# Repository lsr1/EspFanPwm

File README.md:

# EspFanPwm

control speed of one to three fans via PWM (9BMB12P2K01) and get the tacho signal, using a D1 mini with [ESPHome](https://esphome.io/) via [Home Assistant](https://www.home-assistant.io/). 

## Executive Summary
* This project offers a solution for providing the same speed signal to up to three fans (9BMB12P2K01) with Home Assistant (via ESPHome), utilizing a D1 mini board.
* This project consists of a KiCad project that gives you the [Gerber files](gerber/gerber.zip) to order a PCB (e.g. at [JLCPCB](https://cart.jlcpcb.com)) onto which (mostly) passive components (pinheaders/sockets) are soldered. Then you plug on some standard modules you can get from [AliExpress](https://www.aliexpress.com), create a device in Home Assistant and are pretty much done.
* For the impatient: Go to [Installation](#Installation).

## Picture

## Sidenotes
This is my third "public GitHub" project. Yeah, I copy/paste a lot of these READMEs... I made something (crude) that I nevertheless think might be useful for somebody else - this time, I think the audience is rather small, but I am publishing it regardless :-). As usual, this readme will be rather long - I want to document the story behind it for my records.</br>
Despite the verbosity of the README, it assumes that you know how to solder, how to work with a multimeter and your way around Home Assistant and ESPHome. Some things here are weirdly specific, while some are infuriatingly generic (assuming a lot of knowhow).

## Preamble (Why)
I did this because a crate of 9BMB12P2K01 fans fell from a truck and into my lap. Without a PWM signal they are really loud, so I wanted to control their speed. As added bonus (and to maybe find out if a fan broke) and because the fans spit this out, I also wanted to monitor the tacho signal.

## Design Decisions (and other reasoning)
### Goals
* Drive three fans with the same speed (no need for different speeds).
* The power of the fans shall not be routed over the PCB (they should be directly connected to a PSU that will also power the board). 
* Have mainly only passive components on the PCB to make it easy to solder.
* Use as many widely available off-the-shelf components and modules as possible over working directly with parts/MCUs.
* Have a compact PCB design.
* Provide separate tacho signal monitoring for each of the up to 3 fans.
* Make all voltages on the board available.
* Enable usage of unused D1 mini pins via pinheaders.
* Have enough GND pins. 
* Have short high-voltage tracks.
* Have everything socketed. 
* Have the antenna of the D1 board protrude over the PCB to avoid interference from PCB copper fill.
* The silkscreen on the board shall be self-speaking for modules over the usual 'short nomenclature' (e.g. "J1"). 
* C1 for stabilizing voltage when the fans turns on should be optional. 
* Large SMD components (THT pullup resistors would have made the board too large).
* Low cost.

### Non-goals
* No need for perfectly aligned mounting holes.
* No need for separate speed PWM signals (all 3 fans can be the same speed).
* Micro-USB port of the D1 does not need to be available when socketed (it just worked out that way here).
* No need for energy efficiency. 
* No need for "perfect" PCB/circuit design (<i>done is better than perfect</i>).

## BOM (for 1 module)
* 1 x PCB (see [Installation](#Installation))
* 1 x D1 Mini (with normal pinheaders looking 'down'; from Ali)
* 1 x 4-lane level shifter (check correct pin-out)
* 1 x MP1584 DC-DC step-down Module with LM2596 (from Ali)
* 1 x KF301- 2Pin 5.0mm screw-terminal (from Ali)
* 2 x 1x8pin female pinheaders 2.54 mm (from Ali)
* 2 x 1x6pin female pinheaders 2.54 mm (from Ali)
* 4 x 1x2pin female pinheaders 2.54 mm (from Ali)
* 3 x 1206_3216 10k SMD resistor (for pullup)

* standard 1 row 2.54mm male pinheaders
* (optional) 1 x capacitor (>= 12V, THT radial D5.0mm / P2.00mm)

## Installation
This will be long. Brace.

### Order PCBs
* Go to [JLCPCB](https://cart.jlcpcb.com/quote) and upload the [gerber.zip](gerber/gerber.zip). Sidenote: I'm neither sponsored nor do I endorse them specifically, I just find them convenient. Make sure you select the correct PCB thickness (1.2 mm). I also set "Remove Order Number" to "Specify a location" (layout contains a field for this). No other special settings.

### Soldering
* Solder the components. No special advice here - it should be pretty straight forward.
* Solder the SMD pullup resistors first.
* If you populate the C1 capacitor, make sure you leave enough 'height' of the legs to fold it down 90 degrees to lie flat (otherwise the A4988 won't fit above).

### Tuning
* <b>BEFORE</b> putting on all modules and connect power, tune the MP1584 to 5V output. Do this <b>now</b>.

### Assemply
* Put all modules on the board. Take care of the orientation - there is absolutely no safeguard against voltage reversal or such things.
* Provide 12V input (VCC is left on the screw terminal, GND is right).
* The 9BMB12P2K01 cables are:

|row #|color|what|D1_mini pin
---| --- | --- | ---
1|BLK|GND | none (PSU directly)
2|RED|VCC (12V) | none (PSU directly)
3|YLW|tacho (output from fan) | D2, D3, D4
4|BRN|PWM signal (input to fan) | D1 (all three fans)

### Software
* It is assumed you have a working instance of Home Assistant with a working ESPHome plugin. If not, please google how to get there.
* Create an ESPHome device in Home Assistant with the configuration as basis noted in [this file](HomeAssistant/EspFanPwm.yaml). Modify to your gusto.

### Caveats / FAQ
* This is not the work of a professional, and thus has not been load/fuzzy/destructive-tested. All things could happen, thus this project comes without any warranty. Never use it anywhere in a production situation.

* You can't solder the MP1584 directly on the board even if you don't care about the mouting-hole: The holes for the pins are too small (only the female pin-headers fit, but no the male pinheaders directly). This might be changed on a v2 of the board.

* The mounting holes are connected to GND because ... no reason. 

* There is intentionally no ESPHome binary provided for download and flashing here.

* I'm neither affiliated with nor do I get money from JLC nor Ali, I just find both convenient. 

* Why is there no YT video describing this whole thing? - B/c IMHO YT sucks for technical documentation. 

* The KiCad project does not have all components/footprints - I got them from various online sources and didn't track the copyright - sorry.

* I found a datasheet for the 9BMB12P2K01, but it is not provided here b/c I don't know how copyright works. 

## License and Legalese
* May be (re)used for personal/private use only and not sold/licensed for commercial or financial gain. This non-standard license should make it impossible and really difficult for commercial enterprises to profit from my work (pay people to design this!), but enable the hobbyist/enthusiast to work with it.
* If I have inadverently (re-)used your work without either properly attributing it or something, please let me know - I'd be happy to correct this.

## Donations
Yes please.

## Feedback
Also yes please! (I hope I figure out how this whole pull-request thing works...)

## Shoutout ...
* ... to [CCC](https://www.ccc.de) and [CCCZH](https://www.ccczh.ch/)!
* ... to all FOSS contributors that helped making SW that enabled me to do this. Nanos gigantium humeris insidentes.

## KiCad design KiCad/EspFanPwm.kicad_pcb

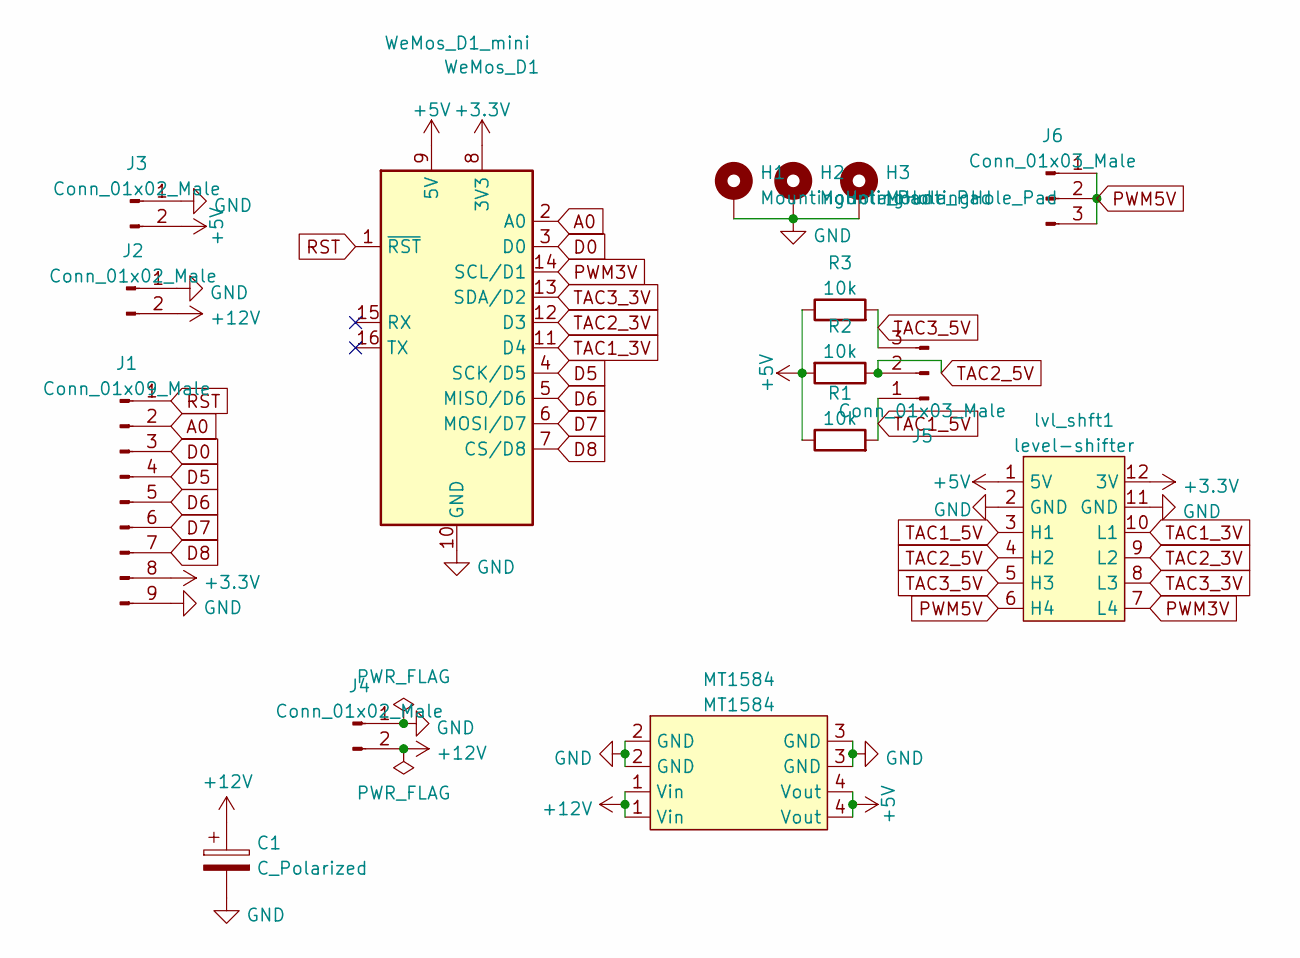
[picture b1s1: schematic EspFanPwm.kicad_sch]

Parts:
C1: C_Polarized; CP_Radial_D5.0mm_P2.00mm
H1, H2, H3: MountingHole_Pad; MountingHole_3.2mm_M3_DIN965_Pad
J1: Conn_01x09_Male; PinHeader_1x09_P2.54mm_Vertical
J2, J3: Conn_01x02_Male; PinHeader_1x02_P2.54mm_Vertical
J4: Conn_01x02_Male; TerminalBlock_bornier-2_P5.08mm
J5, J6: Conn_01x03_Male; PinHeader_1x03_P2.54mm_Vertical
MT1584: MT1584; MP1584_buck_module
R1, R2, R3: 10k; R_1206_3216Metric_Pad1.30x1.75mm_HandSolder
WeMos_D1: WeMos_D1_mini; WEMOS_D1_mini_light
lvl_shft1: level-shifter

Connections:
+3V3: J1.8, WeMos_D1.8 (3V3), lvl_shft1.12 (3V)
+5V: J3.2, MT1584.4 (Vout), R1.1, R2.2, R3.1, WeMos_D1.9 (5V), lvl_shft1.1 (5V)
+12V: C1.1, J2.2, J4.2, MT1584.1 (Vin)
A0: J1.2, WeMos_D1.2 (A0)
D0: J1.3, WeMos_D1.3 (D0)
D5: J1.4, WeMos_D1.4 (SCK/D5)
D6: J1.5, WeMos_D1.5 (MISO/D6)
D7: J1.6, WeMos_D1.6 (MOSI/D7)
D8: J1.7, WeMos_D1.7 (CS/D8)
GND: C1.2, H1.1, H2.1, H3.1, J1.9, J2.1, J3.1, J4.1, MT1584.2 (GND), MT1584.3 (GND), WeMos_D1.10 (GND), lvl_shft1.2 (GND), lvl_shft1.11 (GND)
PWM3V: WeMos_D1.14 (SCL/D1), lvl_shft1.7 (L4)
PWM5V: J6.1, J6.2, J6.3, lvl_shft1.6 (H4)
RST: J1.1, WeMos_D1.1 (~RST)
TAC1_3V: WeMos_D1.11 (D4), lvl_shft1.10 (L1)
TAC1_5V: J5.1, R1.2, lvl_shft1.3 (H1)
TAC2_3V: WeMos_D1.12 (D3), lvl_shft1.9 (L2)
TAC2_5V: J5.2, R2.1, lvl_shft1.4 (H2)
TAC3_3V: WeMos_D1.13 (SDA/D2), lvl_shft1.8 (L3)
TAC3_5V: J5.3, R3.2, lvl_shft1.5 (H3)

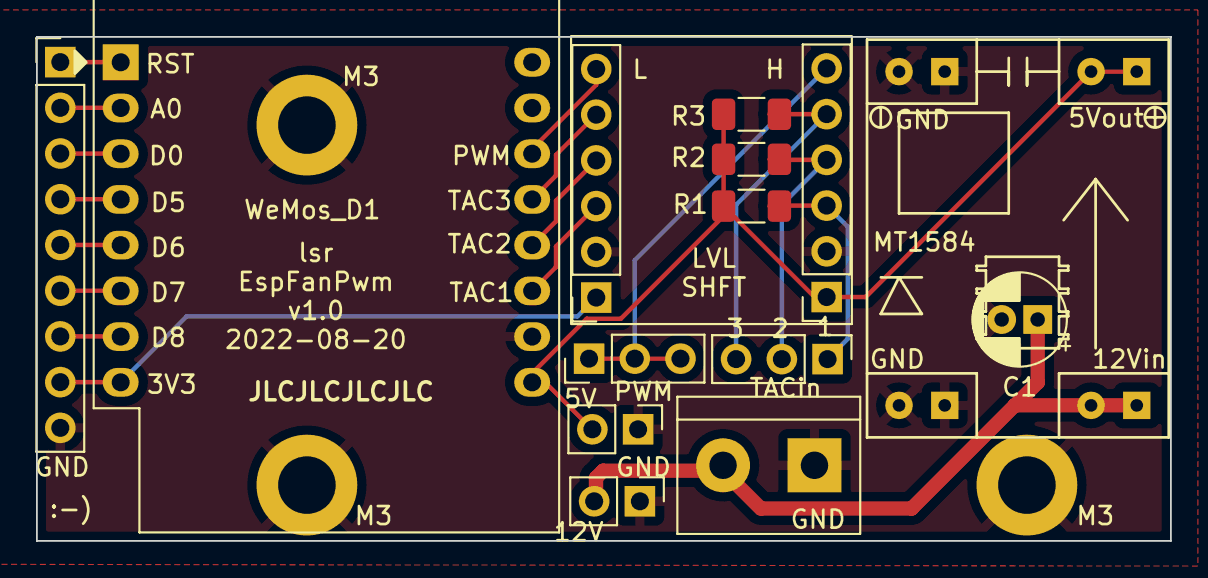
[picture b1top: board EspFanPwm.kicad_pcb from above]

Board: 2 copper layers, 63.0 x 28.0 mm, 16 parts (0 on the bottom side), 19 nets.
